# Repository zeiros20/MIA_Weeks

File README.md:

# MIA_Weeks
MIA 5 weeks training

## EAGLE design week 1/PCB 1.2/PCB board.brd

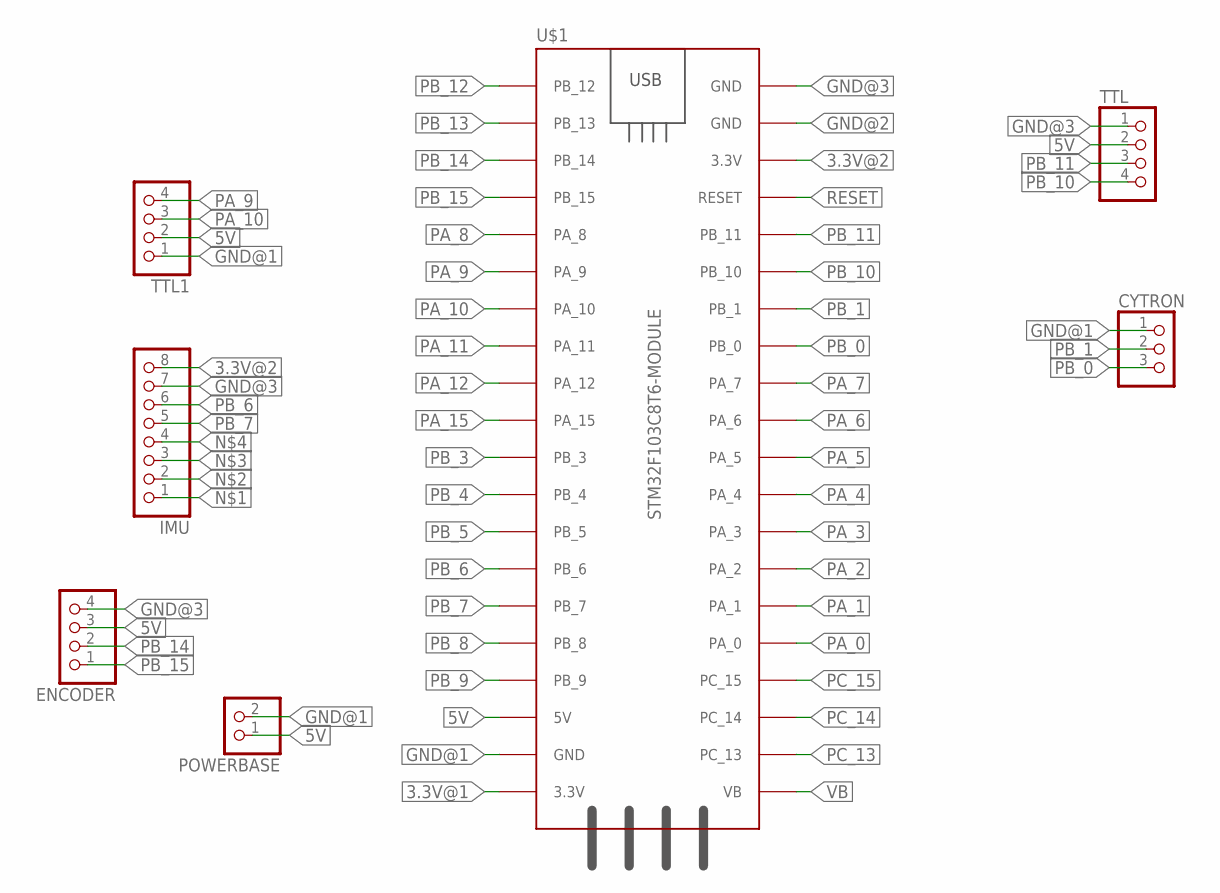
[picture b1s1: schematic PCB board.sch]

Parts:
CYTRON: PINHD-1X3; 1X03
ENCODER: PINHD-4_DATA; 1X04_DATA
IMU: PINHD-1X8; 1X08
POWERBASE: PINHD-1X2; 1X02
TTL, TTL1: PINHD-4_DATA; 1X04_DATA
U$1: STM32F103C8T6-MODULE

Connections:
3.3V@1: U$1.3.3V_1 (3.3V)
3.3V@2: IMU.8, U$1.3.3V_2 (3.3V)
5V: ENCODER.3, POWERBASE.1, TTL.2, TTL1.2, U$1.5V
GND@1: CYTRON.1, POWERBASE.2, TTL1.1, U$1.GND_1 (GND)
GND@2: U$1.GND_2 (GND)
GND@3: ENCODER.4, IMU.7, TTL.1, U$1.GND_3 (GND)
PA_0: U$1.PA_0
PA_1: U$1.PA_1
PA_2: U$1.PA_2
PA_3: U$1.PA_3
PA_4: U$1.PA_4
PA_5: U$1.PA_5
PA_6: U$1.PA_6
PA_7: U$1.PA_7
PA_8: U$1.PA_8
PA_9: TTL1.4, U$1.PA_9
PA_10: TTL1.3, U$1.PA_10
PA_11: U$1.PA_11
PA_12: U$1.PA_12
PA_15: U$1.PA_15
PB_0: CYTRON.3, U$1.PB_0
PB_1: CYTRON.2, U$1.PB_1
PB_3: U$1.PB_3
PB_4: U$1.PB_4
PB_5: U$1.PB_5
PB_6: IMU.6, U$1.PB_6
PB_7: IMU.5, U$1.PB_7
PB_8: U$1.PB_8
PB_9: U$1.PB_9
PB_10: TTL.4, U$1.PB_10
PB_11: TTL.3, U$1.PB_11
PB_12: U$1.PB_12
PB_13: U$1.PB_13
PB_14: ENCODER.2, U$1.PB_14
PB_15: ENCODER.1, U$1.PB_15
PC_13: U$1.PC_13
PC_14: U$1.PC_14
PC_15: U$1.PC_15
RESET: U$1.RESET
VB: U$1.VB

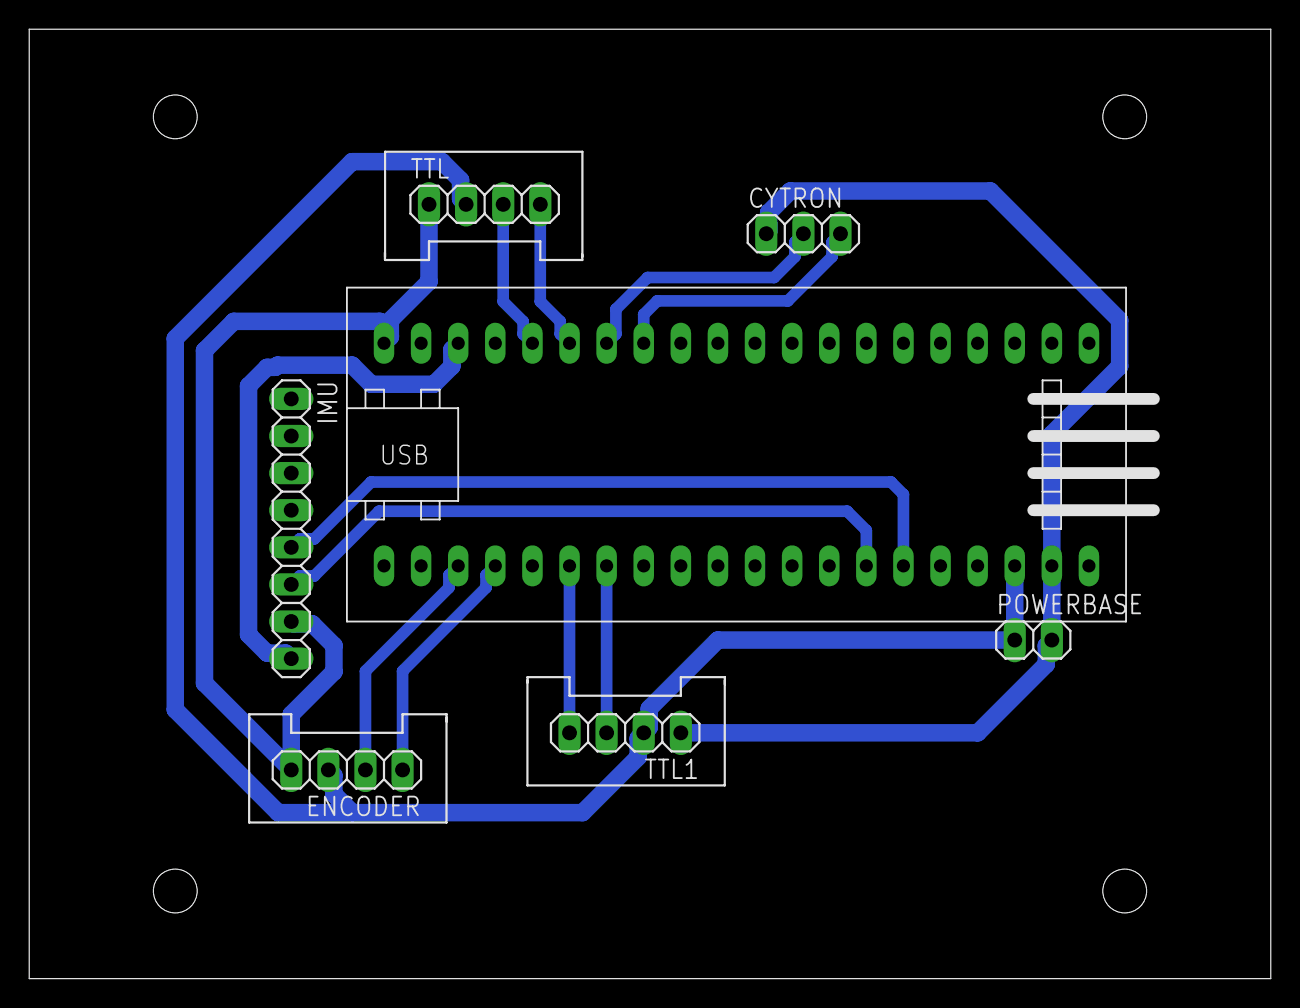
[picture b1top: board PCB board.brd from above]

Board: 2 copper layers, 85.0 x 65.0 mm, 7 parts (0 on the bottom side), 14 nets.

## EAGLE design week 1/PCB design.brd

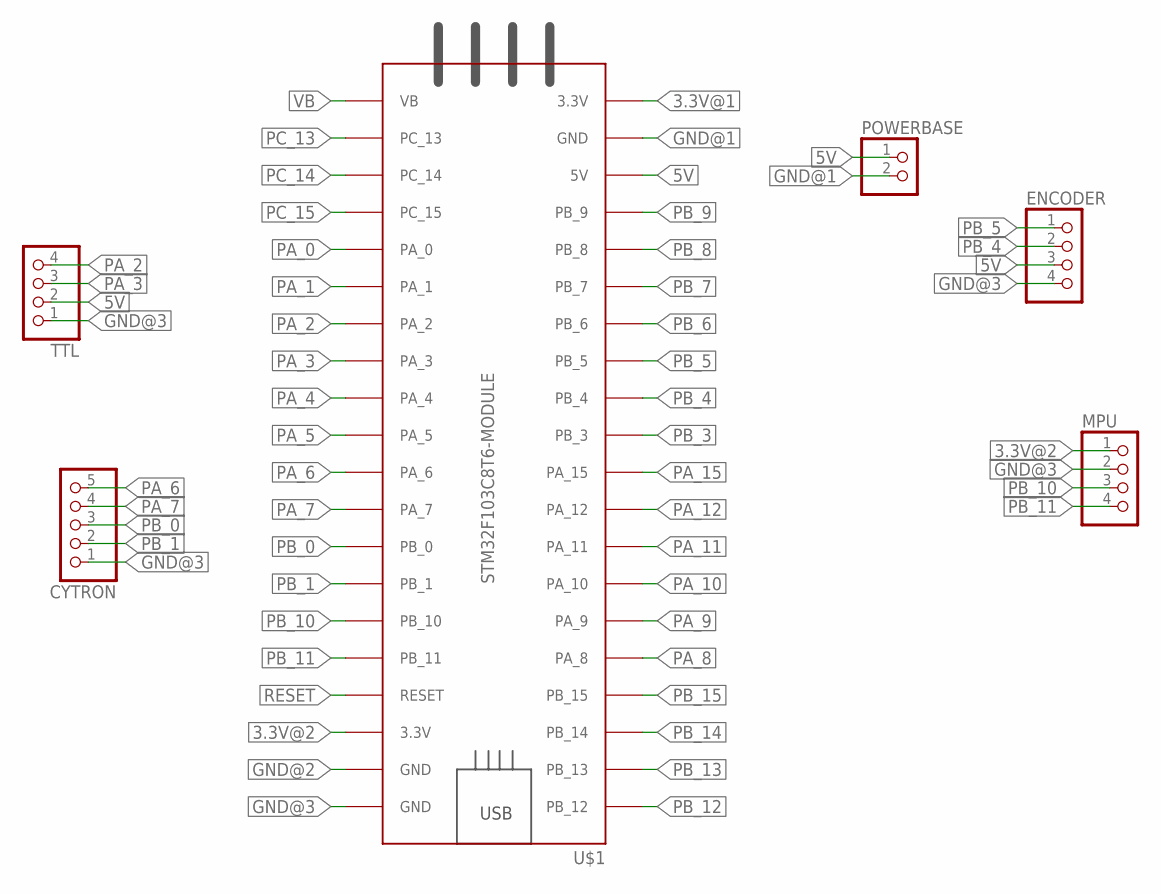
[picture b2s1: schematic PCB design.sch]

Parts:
CYTRON: PINHD-1X5; 1X05
ENCODER: PINHD-1X4; 1X04
MPU: PINHD-1X4; 1X04
POWERBASE: PINHD-1X2; 1X02
TTL: PINHD-1X4; 1X04
U$1: STM32F103C8T6-MODULE

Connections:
3.3V@1: U$1.3.3V_1 (3.3V)
3.3V@2: MPU.1, U$1.3.3V_2 (3.3V)
5V: ENCODER.3, POWERBASE.1, TTL.2, U$1.5V
GND@1: POWERBASE.2, U$1.GND_1 (GND)
GND@2: U$1.GND_2 (GND)
GND@3: CYTRON.1, ENCODER.4, MPU.2, TTL.1, U$1.GND_3 (GND)
PA_0: U$1.PA_0
PA_1: U$1.PA_1
PA_2: TTL.4, U$1.PA_2
PA_3: TTL.3, U$1.PA_3
PA_4: U$1.PA_4
PA_5: U$1.PA_5
PA_6: CYTRON.5, U$1.PA_6
PA_7: CYTRON.4, U$1.PA_7
PA_8: U$1.PA_8
PA_9: U$1.PA_9
PA_10: U$1.PA_10
PA_11: U$1.PA_11
PA_12: U$1.PA_12
PA_15: U$1.PA_15
PB_0: CYTRON.3, U$1.PB_0
PB_1: CYTRON.2, U$1.PB_1
PB_3: U$1.PB_3
PB_4: ENCODER.2, U$1.PB_4
PB_5: ENCODER.1, U$1.PB_5
PB_6: U$1.PB_6
PB_7: U$1.PB_7
PB_8: U$1.PB_8
PB_9: U$1.PB_9
PB_10: MPU.3, U$1.PB_10
PB_11: MPU.4, U$1.PB_11
PB_12: U$1.PB_12
PB_13: U$1.PB_13
PB_14: U$1.PB_14
PB_15: U$1.PB_15
PC_13: U$1.PC_13
PC_14: U$1.PC_14
PC_15: U$1.PC_15
RESET: U$1.RESET
VB: U$1.VB

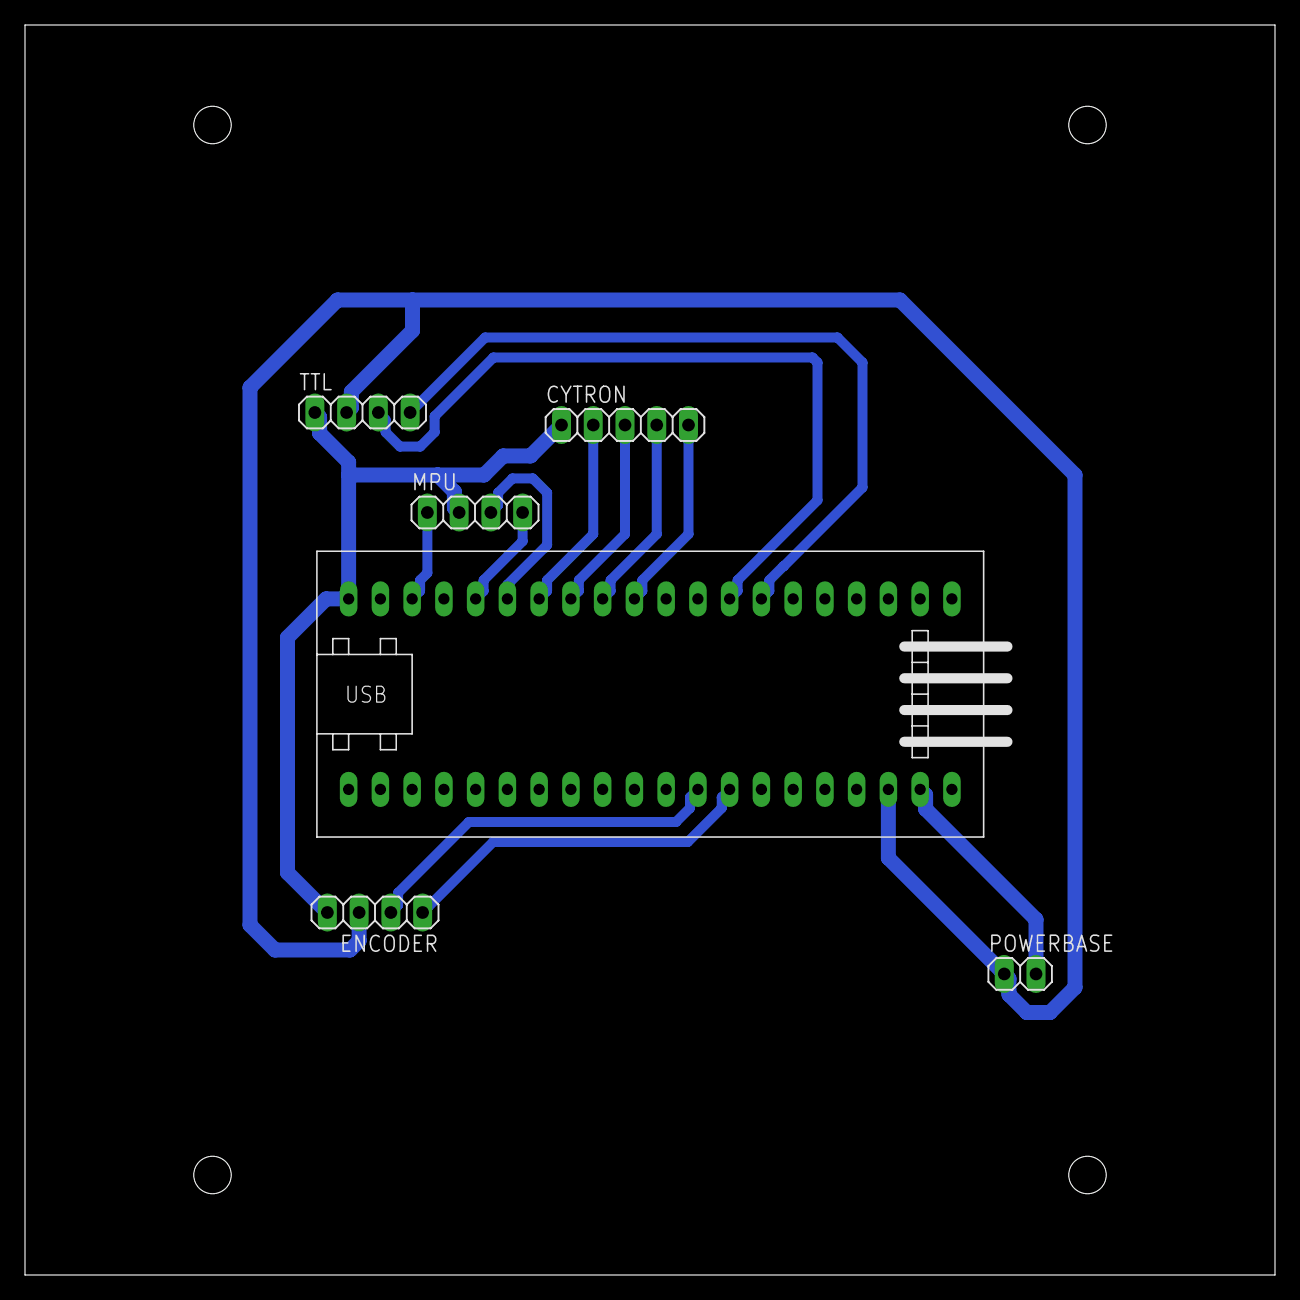
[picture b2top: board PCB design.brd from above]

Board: 2 copper layers, 100.0 x 100.0 mm, 6 parts (0 on the bottom side), 14 nets.

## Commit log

2022-02-08 Create MPC
2022-02-09 Create MPC_2
2022-03-23 Set theme jekyll-theme-midnight
